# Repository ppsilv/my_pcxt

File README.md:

# my_pcxt
A try to make a pc-xt board with SRAM

## PC-XT I/O Addresses

PIC 8259
The PC/XT ISA system has one 8259 controller, and the port numbers for
configuring it are:
    Port 0x20: The master PIC's port A
    Port 0x21: The master PIC's port B

The IBM PC XT uses a single 8259 Programmable Interrupt Controller (PIC)
chip that interfaces with the system through the following I/O locations:
Ports 20h/0A0h: The command register, which is write only, and the status
register, which is read only
Ports 21h/0A1h: Corresponds to the slave PIC
8259 – The eCS Dump
The BIOS traditionally maps the 8259 PIC's eight interrupt requests (IRQs)
to interrupts 8 to 15 (0x08 to 0x0F).
The PIC manages hardware interrupt requests in an interrupt driven system
environment. When an I/O device requires service, it signals the PIC via
one of the PIC's seven interrupt request (IR) input lines. The PIC then
activates the INT line, which is connected to the CPU INTR line.

TIMER 8253
On PCs the address for timer0 (chip) is at port 40h..43h and the second
timer1 (chip) is at 50h..53h.
    Port 40h
    Port 41h
    Port 42h
    Port 43h

On x86 PCs, many video card BIOS and system BIOS will reprogram the second
counter for their own use. Reprogramming typically happens during video mode
changes, when the video BIOS may be executed, and during system management
mode and power saving state changes, when the system BIOS may be executed.
This prevents any serious alternative uses of the timer's second counter on
many x86 systems.

As stated above, Channel 0 is implemented as a counter. Typically, the
initial value of the counter is set by sending bytes to the Control, then
Data I/O Port registers (the value 36h sent to port 43h, then the low byte
to port 40h, and port 40h again for the high byte). The counter counts down
to zero, then sends a hardware interrupt (IRQ 0, INT 8) to the CPU. The
counter then resets to its initial value and begins to count down again.
The fastest possible interrupt frequency is a little over a half of a
megahertz. The slowest possible frequency, which is also the one normally
used by computers running MS-DOS or compatible operating systems, is about
18.2 Hz. Under these real mode operating systems, the BIOS accumulates the
number of INT 8 calls that it receives in real mode address 0040:006c, which
can be read by a program.

Parallel Port
    LPT1: 0x378 (or occasionally 0x3BC) (IRQ 7)
    LPT2: 0x278 (IRQ 6).

IBM defined three standard port base addresses for the parallel printer port
in the IBM PC:
Port R/W IOAddr Bits Function: Data Out W Base+0 D0-D7 8 LS TTL outputs
Status In R Base+1 S3-S7 5 LS TTL inputs
Control Out W Base+2 C0-C3 4 TTL Open Collector outputs
Common base addresses for parallel ports include:
    LPT1: 0x378 (or occasionally 0x3BC) (IRQ 7)
    LPT2: 0x278 (IRQ 6).
A parallel port is a type of interface that allows computers to connect to
various peripherals. The most common configuration for a standard parallel
port is the Centronics port, which has 25 pins.

PORTS Common I/O Port Addresses

	Port addresses are not always constant across PC, AT and PS/2
	Unless marked, port addresses are relative to PC and XT only

	000-00F  8237 DMA controller
	000 Channel 0 address register
	001 Channel 0 word count
	002 Channel 1 address register
	003 Channel 1 word count
	004 Channel 2 address register
	005 Channel 2 word count
	006 Channel 3 address register
	007 Channel 3 word count
	008 Status/command register
	009 Request register
	00A Mask register
	00B Mode register
	00C Clear MSB/LSB flip flop
	00D Master clear temp register
	00E Clear mask register
	00F Multiple mask register

	020-02F  8259A Master Programmable Interrupt Controller
	020 8259 Command port  (see 8259)
	021 8259 Interrupt mask register  (see 8259)

	040-05F  8253 or 8254 Programmable Interval Timer (PIT, see ~8253~)
	040 8253 channel 0, counter divisor
	041 8253 channel 1, RAM refresh counter
	042 8253 channel 2, Cassette and speaker functions
	043 8253 mode control  (see 8253)
	044 8254 PS/2 extended timer
	047 8254 Channel 3 control byte

	060 8255 Port A keyboard input/output buffer (output PCjr)
	061 8255 Port B output
	062 8255 Port C input
	063 8255 Command/Mode control register

//	060-06F  8042 Keyboard Controller  (AT,PS/2)
//	060 8042 Keyboard input/output buffer register
//	061 8042 system control port (for compatability with 8255)
//	064 8042 Keyboard command/status register

	070 CMOS RAM/RTC, also NMI enable/disable (AT,PS/2, see RTC)
	071 CMOS RAM data  (AT,PS/2)

	080 Manufacturer systems checkpoint port (used during POST)
	080-090  DMA Page Registers
	081 High order 4 bits of DMA channel 2 address
	082 High order 4 bits of DMA channel 3 address
	083 High order 4 bits of DMA channel 1 address

	090-097  POS/Programmable Option Select  (PS/2)
	090 Central arbitration control Port
	091 Card selection feedback
	092 System control and status register
	094 System board enable/setup register
	095 Reserved
	096 Adapter enable/setup register
	097 Reserved

	0A0 NMI Mask Register (PC,XT) (write 80h to enable NMI, 00h disable)
	0A0-0BF  Second 8259 Programmable Interrupt Controller (AT, PS/2)
	0A0 Second 8259 Command port  (see 8259)
	0A1 Second 8259 Interrupt mask register  (see 8259)

	0C0 TI SN76496 Programmable Tone/Noise Generator (PCjr)
	0C0-0DF  8237 DMA controller 2 (AT)
	0C2 DMA channel 3 selector  (see ports 6 & 82)

	0E0-0EF  Reserved

	0F0-0FF  Math coprocessor (AT, PS/2)
	0F0-0F5  PCjr Disk Controller
	0F0 Disk Controller
	0F2 Disk Controller control port
	0F4 Disk Controller status register
	0F5 Disk Controller data port

	0F8-0FF  Reserved for future microprocessor extensions

	100-10F  POS Programmable Option Select (PS/2)
	100 POS Register 0, Adapter ID byte (LSB)
	101 POS Register 1, Adapter ID byte (MSB)
	102 POS Register 2, Option select data byte 1
	    Bit 0 is card enable (CDEN)
	103 POS Register 3, Option select data byte 2
	104 POS Register 4, Option select data byte 3
	105 POS Register 5, Option select data byte 4
	    Bit 7 is (-CHCK)
	    Bit 6 is reserved
	106 POS Register 6, subaddress extension (LSB)
	107 POS Register 7, subaddress extension (MSB)

	110-1EF  System I/O channel

	170-17F  Fixed disk 1 (AT)
	170 disk 1 data
	171 disk 1 error
	172 disk 1 sector count
	173 disk 1 sector number
	174 disk 1 cylinder low
	175 disk 1 cylinder high
	176 disk 1 drive/head
	177 disk 1 status

	1F0-1FF  Fixed disk 0 (AT)
	1F0 disk 0 data
	1F1 disk 0 error
	1F2 disk 0 sector count
	1F3 disk 0 sector number
	1F4 disk 0 cylinder low
	1F5 disk 0 cylinder high
	1F6 disk 0 drive/head
	1F7 disk 0 status

	200-20F  Game Adapter (see GAME PORT or ~JOYSTICK~)

	210-217  Expansion Card Ports (XT)
	210 Write: latch expansion bus data
	    read:  verify expansion bus data
	211 Write: clear wait,test latch
	    Read:  MSB of data address
	212 Read:  LSB of data address
	213 Write: 0=enable, 1=/disable expansion unit
	214-215  Receiver Card Ports
	214 write: latch data, read: data
	215 read:  MSB of address, next read: LSB of address

	21F Reserved

	220-26F  Reserved for I/O channel

	270-27F  Third parallel port (see ~PARALLEL PORT~)
	278 data port
	279 status port
	27A control port

	280-2AF  Reserved for I/O channel

	2A2-2A3  MSM58321RS clock

	2B0-2DF  Alternate EGA, or 3270 PC video (XT, AT)

	2E0 Alternate EGA/VGA
	2E1 GPIB Adapter  (AT)

	2E2-2E3  Data acquisition adapter (AT)

	2E8-2EF  COM4 non PS/2 UART (Reserved by IBM) (see ~UART~)

	2F0-2F7  Reserved

	2F8-2FF  COM2 Second Asynchronous Adapter (see UART)
		 Primary Asynchronous Adapter for PCjr

	300-31F  Prototype Experimentation Card (except PCjr)
		 Periscope hardware debugger
	320-32F  Hard Disk Controller  (XT)
	320 Read from/Write to controller
	321 Read: Controller Status, Write: controller reset
	322 Write: generate controller select pulse
	323 Write: Pattern to DMA and interrupt mask register
	    (see ports 0F,21,C2)
	324 disk attention/status

	330-33F  Reserved for XT/370

	340-35F  Reserved for I/O channel

	360-36F  PC Network

	370-377  Floppy disk controller (except PCjr)
	372 Diskette digital output
	374 Diskette controller status
	375 Diskette controller data
	376 Diskette controller data
	377 Diskette digital input

	378-37F  Second Parallel Printer (see ~PARALLEL PORT~)
		 First Parallel Printer (see PARALLEL PORT)
	378 data port
	379 status port
	37A control port

	380-38F  Secondary Binary Synchronous Data Link Control (SDLC) adapter
	380 On board 8255 port A, internal/external sense
	381 On board 8255 port B, external modem interface
	382 On board 8255 port C, internal control and gating
	383 On board 8255 mode register
	384 On board 8253 channel square wave generator
	385 On board 8253 channel 1 inactivity time-out
	386 On board 8253 channel 2 inactivity time-out
	387 On board 8253 mode register
	388 On board 8273 read: status; Write: Command
	389 On board 8273 write: parameter; read: response
	38A On board 8273 transmit interrupt status
	38B On board 8273 receiver interrupt status
	38C On board 8273 data

	390-39F  Cluster Adapter

	3A0-3AF  Primary Binary Synchronous Data Link Control (SDLC) adapter
	3A0 On board 8255 port A, internal/external sense
	3A1 On board 8255 port B, external modem interface
	3A2 On board 8255 port C, internal control and gating
	3A3 On board 8255 mode register
	3A4 On board 8253 counter 0 unused
	3A5 On board 8253 counter 1 inactivity time-outs
	3A6 On board 8253 counter 2 inactivity time-outs
	3A7 On board 8253 mode register
	3A8 On board 8251 data
	3A9 On board 8251 command/mode/status register

	3B0-3BF Monochrome Display Adapter (write only, see ~6845~)
	3B0 port address decodes to 3B4
	3B1 port address decodes to 3B5
	3B2 port address decodes to 3B4
	3B3 port address decodes to 3B5
	3B4 6845 index register, selects which register [0-11h]
	    is to be accessed through port 3B5
	3B5 6845 data register [0-11h] selected by port 3B4,
	    registers 0C-0F may be read.  If a read occurs without
	    the adapter installed, FFh is returned.  (see 6845)
	3B6 port address decodes to 3B4
	3B7 port address decodes to 3B5
	3B8 6845 Mode control register
	3B9 reserved for color select register on color adapter
	3BA status register (read only)
	3BB reserved for light pen strobe reset

	3BC-3BF  Primary Parallel Printer Adapter (see ~PARALLEL PORT~)
	3BC parallel 1, data port
	3BD parallel 1, status port
	3BE parallel 1, control port

	3C0-3CF  EGA/VGA
	3C0 VGA attribute and sequencer register
	3C1 Other video attributes
	3C2 EGA, VGA, CGA input status 0
	3C3 Video subsystem enable
	3C4 CGA, EGA, VGA sequencer index
	3C5 CGA, EGA, VGA sequencer
	3C6 VGA video DAC PEL mask
	3C7 VGA video DAC state
	3C8 VGA video DAC PEL address
	3C9 VGA video DAC
	3CA VGA graphics 2 position
	3CC VGA graphics 1 position
	3CD VGA feature control
	3CE VGA graphics index
	3CF Other VGA graphics

	3D0-3DF Color Graphics Monitor Adapter (ports 3D0-3DB are
		write only, see 6845)
	3D0 port address decodes to 3D4
	3D1 port address decodes to 3D5
	3D2 port address decodes to 3D4
	3D3 port address decodes to 3D5
	3D4 6845 index register, selects which register [0-11h]
	    is to be accessed through port 3D5
	3D5 6845 data register [0-11h] selected by port 3D4,
	    registers 0C-0F may be read.  If a read occurs without
	    the adapter installed, FFh is returned.  (see 6845)
	3D6 port address decodes to 3D4
	3D7 port address decodes to 3D5
	3D8 6845 Mode control register (CGA, EGA, VGA, except PCjr)
	3D9 color select palette register (CGA, EGA, VGA, see 6845)
	3DA status register (read only, see 6845, PCjr VGA access)
	3DB Clear light pen latch (any write)
	3DC Preset Light pen latch
	3DF CRT/CPU page register (PCjr only)

	3E8-3EF  COM3 non PS/2 UART (Reserved by IBM) (see ~UART~)

	3F0-3F7  Floppy disk controller (except PCjr)
	3F0 Diskette controller status A
	3F1 Diskette controller status B
	3F2 controller control port
	3F4 controller status register
	3F5 data register (write 1-9 byte command, see INT 13)
	3F6 Diskette controller data
	3F7 Diskette digital input

	3F8-3FF  COM1 Primary Asynchronous Adapter  (see ~UART~)

	3220-3227  PS/2 COM3 (see UART)
	3228-322F  PS/2 COM4 (see UART)
	4220-4227  PS/2 COM5 (see UART)
	4228-422F  PS/2 COM6 (see UART)
	5220-5227  PS/2 COM7 (see UART)
	5228-522F  PS/2 COM8 (see UART)

	- many cards designed for the ISA BUS only uses the lower 10 bits
	  of the port address but some ISA adapters use addresses beyond
	  3FF.  Any address that matches in the lower 10 bits will decode
	  to the same card.   It is up to the adapters to resolve or ignore
	  the high bits of the port addresses.   An example would be the
	  Cluster adapter that has a port address of 390h.  The second
	  cluster adapter has a port address of 790h which resolves to
	  the same port address with the cards determining which one
	  actually gets the data.

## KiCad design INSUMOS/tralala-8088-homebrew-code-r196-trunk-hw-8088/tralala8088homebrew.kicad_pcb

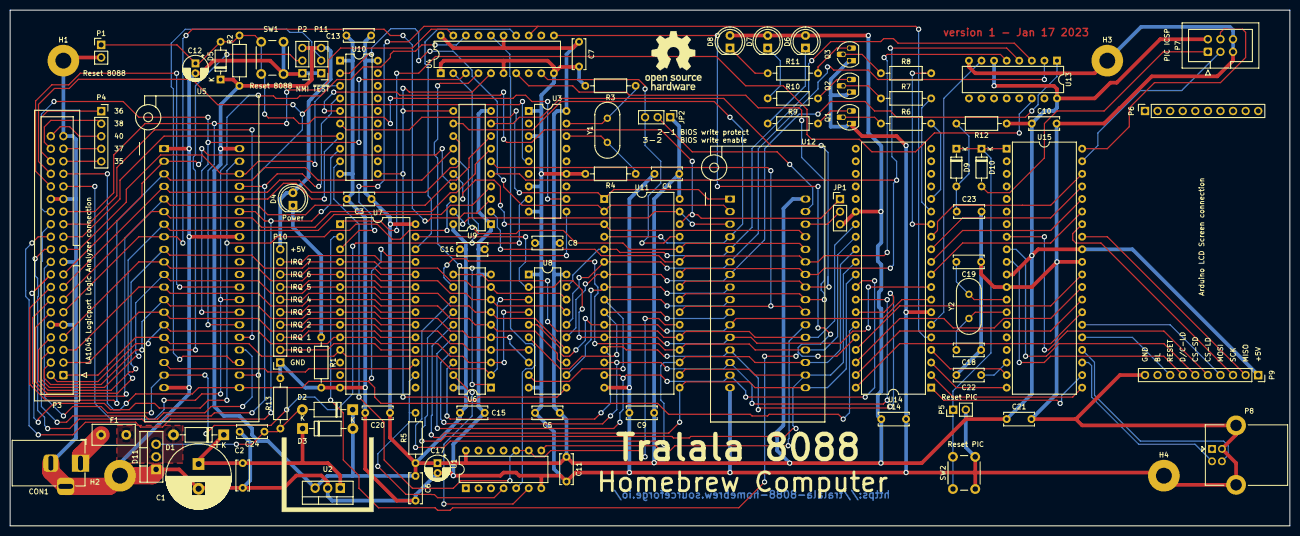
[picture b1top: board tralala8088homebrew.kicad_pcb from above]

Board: 2 copper layers, 258.4 x 104.1 mm, 89 parts (0 on the bottom side), 139 nets.

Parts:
C1: 1000 uF; CP_Radial_D13.0mm_P5.00mm
C2: 330nF; C_Disc_D6.0mm_W2.5mm_P5.00mm
C3, C4, C5, C6, C7, C8, C9, C10, C11, C13, C14, C15, C16, C20, C21, C23, C24: 100nF; C_Disc_D6.0mm_W2.5mm_P5.00mm
C12: 4.7uF; CP_Radial_D5.0mm_P2.00mm
C17: 100uF; CP_Radial_D5.0mm_P2.00mm
C18, C19: 22pF; C_Disc_D6.0mm_W2.5mm_P5.00mm
C22: 220nF; C_Disc_D6.0mm_W2.5mm_P5.00mm
CON1: BARREL_JACK; BarrelJack_Horizontal
D1: 1N4002; D_DO-41_SOD81_P10.16mm_Horizontal
D2: 5.6 V; D_DO-41_SOD81_P10.16mm_Horizontal
D3: D; D_DO-41_SOD81_P10.16mm_Horizontal
D4: Power; LED_D5.0mm
D5, D9, D10: 1N4148; D_DO-35_SOD27_P7.62mm_Horizontal
D6: LED_RED; LED_D5.0mm
D7: LED_YELLOW; LED_D5.0mm
D8: LED_GREEN; LED_D5.0mm
D11: BT151-500RT.127; TO-220-3_Vertical
F1: 30R160U; Fuse_Littelfuse_395Series
H1, H2, H3, H4: MountingHole_Pad; MountingHole_3.2mm_M3_Pad
JP1: ROM type sel; PinHeader_1x03_P2.54mm_Vertical
JP2: Flash Write Protect; PinHeader_1x03_P2.54mm_Vertical
P1, P5: Conn_01x02_Male; PinHeader_1x02_P2.54mm_Vertical
P2: NMI; PinHeader_1x03_P2.54mm_Vertical
P3: LA1034 Logicport Connection; IDC-Header_2x20_P2.54mm_Vertical
P4: Conn_01x05_Female; PinSocket_1x05_P2.54mm_Vertical
P6, P9: CONN_01X10; PinSocket_1x10_P2.54mm_Vertical
P7: PIC ISP; IDC-Header_2x03_P2.54mm_Vertical
P8: USB_B; USB_B_Lumberg_2411_02_Horizontal
P10: Conn_01x10; PinSocket_1x10_P2.54mm_Vertical
P11: ~{TEST}; PinHeader_1x03_P2.54mm_Vertical
Q1, Q2, Q3: 2N3904; TO-92_HandSolder
R1: 270; R_Axial_DIN0207_L6.3mm_D2.5mm_P10.16mm_Horizontal
R2, R6, R7, R8: 10K; R_Axial_DIN0207_L6.3mm_D2.5mm_P10.16mm_Horizontal
R3, R4: 510; R_Axial_DIN0207_L6.3mm_D2.5mm_P10.16mm_Horizontal
R5: 4.7K; R_Axial_DIN0207_L6.3mm_D2.5mm_P10.16mm_Horizontal
R9, R10, R11: 100; R_Axial_DIN0207_L6.3mm_D2.5mm_P10.16mm_Horizontal
R12: 47K; R_Axial_DIN0207_L6.3mm_D2.5mm_P10.16mm_Horizontal
R13: 1k; R_Axial_DIN0207_L6.3mm_D2.5mm_P10.16mm_Horizontal
SW1: RESET_8088; SW_PUSH_6mm_H5mm
SW2: RESET_PIC; SW_PUSH_6mm_H5mm
U1: 74HCT00; DIP-14_W7.62mm
U2: 7805; TO-220-3_Vertical
U3: 8284; DIP-18_W7.62mm
U4: 8288; DIP-20_W7.62mm
U5: 8088; DIP_Socket-40_W11.9_W12.7_W15.24_W17.78_W18.5_3M_240-1280-0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
U6: 74HCT245; DIP-20_W7.62mm
U7: 8259A; DIP-28_W15.24mm
U8, U9, U10: 74HCT373; DIP-20_W7.62mm
U11: AS6C4008; DIP-32_W15.24mm
U12: SST39SF040; DIP_Socket-32_W11.9_W12.7_W15.24_W17.78_W18.5_3M_232-1285-0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
U13: 74HCT138; DIP-16_W7.62mm
U14: 82C55A; DIP-40_W15.24mm
U15: PIC18(L)F4550-I/P or PIC18(L)F4553-I/P; DIP-40_W15.24mm
Y1: 6-30 MHz; Crystal_HC49-U_Vertical
Y2: 20.000 MHz; Crystal_HC49-U_Vertical

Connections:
+5V: C3.1, C4.1, C5.1, C6.1, C7.1, C8.1, C9.1, C10.1, C11.1, C13.1, C14.1, C15.1, C16.1, C17.1, C20.1, C21.1, D2.1 (K), D3.2 (A), D4.2 (A), D5.1 (K), D6.2 (A), D7.2 (A), D8.2 (A), JP1.3 (B), JP2.1 (A), P2.3, P7.2, P9.1, P10.10, P11.3, R2.1, R5.1, R12.1, U1.14 (VCC), U2.3 (OUT), U3.18 (VCC), U4.15 (CEN), U4.20 (VCC), U5.40 (VCC), U6.20 (VCC), U7.28 (VCC), U8.20 (VCC), U9.20 (VCC), U10.20 (VCC), U11.32 (VCC), U12.32 (VCC), U13.6 (E3), U13.16 (VCC), U14.26 (VCC), U15.11 (VDD), U15.32 (VDD)
/8088 System/8255_CS: U13.7 (O7), U14.6 (~CS)
/8088 System/8259A_CS: U7.1 (~CS), U13.14 (O1)
/8088 System/8259A_SP_EN: R5.2, U1.4, U7.16 (~SP/~EN)
/8088 System/A8: P3.11, U5.8 (A8), U9.3 (D0)
/8088 System/A9: P3.12, U5.7 (A9), U9.4 (D1)
/8088 System/A10: P3.13, U5.6 (A10), U9.7 (D2)
/8088 System/A11: P3.14, U5.5 (A11), U9.8 (D3)
/8088 System/A12: P3.15, U5.4 (A12), U9.13 (D4)
/8088 System/A13: P3.16, U5.3 (A13), U9.14 (D5)
/8088 System/A14: P3.17, U5.2 (A14), U9.17 (D6)
/8088 System/A15: P3.18, U5.39 (A15), U9.18 (D7)
/8088 System/A16_S3: P3.21, U5.38 (A16/S3), U10.3 (D0)
/8088 System/A17_S4: P3.22, U5.37 (A17/S4), U10.4 (D1)
/8088 System/A18_S5: P3.23, U5.36 (A18/S5), U10.7 (D2)
/8088 System/A19_S6: P3.24, U5.35 (A19/S6), U10.8 (D3)
/8088 System/AD0: P3.1, U5.16 (AD0), U6.2 (A0), U7.11 (D0), U8.3 (D0)
/8088 System/AD1: P3.2, U5.15 (AD1), U6.3 (A1), U7.10 (D1), U8.4 (D1)
/8088 System/AD2: P3.3, U5.14 (AD2), U6.4 (A2), U7.9 (D2), U8.7 (D2)
/8088 System/AD3: P3.4, U5.13 (AD3), U6.5 (A3), U7.8 (D3), U8.8 (D3)
/8088 System/AD4: P3.5, U5.12 (AD4), U6.6 (A4), U7.7 (D4), U8.13 (D4)
/8088 System/AD5: P3.6, U5.11 (AD5), U6.7 (A5), U7.6 (D5), U8.14 (D5)
/8088 System/AD6: P3.7, U5.10 (AD6), U6.8 (A6), U7.5 (D6), U8.17 (D6)
/8088 System/AD7: P3.8, U5.9 (AD7), U6.9 (A7), U7.4 (D7), U8.18 (D7)
/8088 System/ALE: U4.5 (ALE), U8.11 (LE), U9.11 (LE), U10.11 (LE)
/8088 System/BUF_A0: U7.27 (A0), U8.2 (O0), U11.12 (A0), U12.12 (A0), U14.9 (A0)
/8088 System/BUF_A1: U8.5 (O1), U11.11 (A1), U12.11 (A1), U14.8 (A1)
/8088 System/BUF_A2: U8.6 (O2), U11.10 (A2), U12.10 (A2)
/8088 System/BUF_A3: U8.9 (O3), U11.9 (A3), U12.9 (A3)
/8088 System/BUF_A4: U8.12 (O4), U11.8 (A4), U12.8 (A4)
/8088 System/BUF_A5: U8.15 (O5), U11.7 (A5), U12.7 (A5), U13.1 (A0)
/8088 System/BUF_A6: U8.16 (O6), U11.6 (A6), U12.6 (A6), U13.2 (A1)
/8088 System/BUF_A7: U8.19 (O7), U11.5 (A7), U12.5 (A7), U13.3 (A2)
/8088 System/BUF_A8: U9.2 (O0), U11.27 (A8), U12.27 (A8), U13.5 (E2)
/8088 System/BUF_A9: U9.5 (O1), U11.26 (A9), U12.26 (A9), U13.4 (E1)
/8088 System/BUF_A10: U9.6 (O2), U11.23 (A10), U12.23 (A10)
/8088 System/BUF_A11: U9.9 (O3), U11.25 (A11), U12.25 (A11)
/8088 System/BUF_A12: U9.12 (O4), U11.4 (A12), U12.4 (A12)
/8088 System/BUF_A13: U9.15 (O5), U11.28 (A13), U12.28 (A13)
/8088 System/BUF_A14: U9.16 (O6), U11.3 (A14), U12.29 (A14)
/8088 System/BUF_A15: U9.19 (O7), U11.31 (A15), U12.3 (A15)
/8088 System/BUF_A16: U10.2 (O0), U11.2 (A16), U12.2 (A16)
/8088 System/BUF_A17: JP1.1 (A), U10.5 (O1), U11.30 (A17)
/8088 System/BUF_A18: U10.6 (O2), U11.1 (A18), U12.1 (A18)
/8088 System/BUF_A19: U1.9, U1.10, U10.9 (O3), U11.22 (CE#)
/8088 System/BUF_D0: U6.18 (B0), U11.13 (DQ0), U12.13 (D0), U14.34 (D0)
/8088 System/BUF_D1: U6.17 (B1), U11.14 (DQ1), U12.14 (D1), U14.33 (D1)
/8088 System/BUF_D2: U6.16 (B2), U11.15 (DQ2), U12.15 (D2), U14.32 (D2)
/8088 System/BUF_D3: U6.15 (B3), U11.17 (DQ3), U12.17 (D3), U14.31 (D3)
/8088 System/BUF_D4: U6.14 (B4), U11.18 (DQ4), U12.18 (D4), U14.30 (D4)
/8088 System/BUF_D5: U6.13 (B5), U11.19 (DQ5), U12.19 (D5), U14.29 (D5)
/8088 System/BUF_D6: U6.12 (B6), U11.20 (DQ6), U12.20 (D6), U14.28 (D6)
/8088 System/BUF_D7: U6.11 (B7), U11.21 (DQ7), U12.21 (D7), U14.27 (D7)
/8088 System/CLK: P3.20, U3.8 (CLK), U4.2 (CLK), U5.19 (CLK)
/8088 System/DEN: U1.5, U4.16 (DEN)
/8088 System/DTR: U4.4 (DT/~R), U6.1 (A->B)
/8088 System/ICH_ACK: U14.11 (PC6), U15.36 (RB3/AN9/CCP2/VPO)
/8088 System/ICH_D0: U14.4 (PA0), U15.19 (SPP0/RD0)
/8088 System/ICH_D1: U14.3 (PA1), U15.20 (SPP1/RD1)
/8088 System/ICH_D2: U14.2 (PA2), U15.21 (SPP2/RD2)
/8088 System/ICH_D3: U14.1 (PA3), U15.22 (SPP3/RD3)
/8088 System/ICH_D4: U14.40 (PA4), U15.27 (SPP4/RD4)
/8088 System/ICH_D5: U14.39 (PA5), U15.28 (P1B/SPP5/RD5)
/8088 System/ICH_D6: U14.38 (PA6), U15.29 (P1C/SPP6/RD6)
/8088 System/ICH_D7: U14.37 (PA7), U15.30 (P1D/SPP7/RD7)
/8088 System/ICH_IBF: U14.12 (PC5), U15.37 (RB4/AN11/KBI0/CSSPP)
/8088 System/ICH_OBF: U14.10 (PC7), U15.35 (RB2/AN8/INT2/VMO)
/8088 System/ICH_STB: U14.13 (PC4), U15.38 (RB5/KBI1/PGM)
/8088 System/INTA: U4.14 (~INTA), U7.26 (~INTA)
/8088 System/INTR: U5.18 (INTR), U7.17 (INT)
/8088 System/IORC: U4.13 (~IORC), U7.3 (~RD), U14.5 (~RD)
/8088 System/IOWC: U4.11 (~IOWC), U7.2 (~WR), U14.36 (~WR)
/8088 System/IRQ0: P10.2, U7.18 (IR0)
/8088 System/IRQ1: P10.3, U7.19 (IR1)
/8088 System/IRQ2: P10.4, U7.20 (IR2)
/8088 System/IRQ3: P10.5, U7.21 (IR3)
/8088 System/IRQ4: P10.6, U7.22 (IR4)
/8088 System/IRQ5: P10.7, U7.23 (IR5)
/8088 System/IRQ6: P10.8, U7.24 (IR6)
/8088 System/IRQ7: P10.9, U7.25 (IR7)
/8088 System/LED_GREEN: R8.2, U14.14 (PC0)
/8088 System/LED_RED: R6.2, U14.16 (PC2)
/8088 System/LED_YELLOW: R7.2, U14.15 (PC1)
/8088 System/LOCK: P3.32, U5.29 (~LOCK)
/8088 System/MRDC: U4.7 (~MRDC), U11.24 (OE#), U12.24 (OE)
/8088 System/MWTC: JP2.3 (B), U4.9 (~MWTC), U11.29 (WE#)
/8088 System/QS0: P3.25, U5.25 (QS0)
/8088 System/QS1: P3.26, U5.24 (QS1)
/8088 System/READY: P3.34, U3.5 (READY), U5.22 (READY)
/8088 System/RESET: P3.33, U3.10 (RESET), U5.21 (RESET), U14.35 (RESET)
/8088 System/S0: P3.27, U4.19 (~S0), U5.26 (~S0)
/8088 System/S1: P3.28, U4.3 (~S1), U5.27 (~S1)
/8088 System/S2: P3.31, U4.18 (~S2), U5.28 (~S2)
/PIC and IO/PIC_PGC: P7.3, U15.39 (RB6/KBI2/PGC)
/PIC and IO/PIC_PGD: P7.4, U15.40 (RB7/KBI3/PGD)
/PIC and IO/PIC_VPP: D10.2 (A), P7.1
/PIC and IO/TFT_D_C: P9.7, U15.10 (OESPP/AN7/RE2)
/PIC and IO/TFT_LCD_CS: P9.5, U15.8 (CK1SPP/AN5/RE0)
/PIC and IO/TFT_MISO: P9.2, U15.33 (RB0/AN12/INT0/FLT0/SDI/SDA)
/PIC and IO/TFT_MOSI: P9.4, U15.26 (SDO/RX/DT/RC7)
/PIC and IO/TFT_Reset: P9.8, U15.25 (TX/CK/RC6)
/PIC and IO/TFT_SCK: P9.3, U15.34 (RB1/AN10/INT1/SCK/SCL)
/PIC and IO/TFT_SD_CS: P9.6, U15.9 (CK2SPP/AN6/RE1)
/Power and Clock/Vin_fused: D1.2 (A), D11.2 (A), F1.2
GND: C1.2, C2.2, C3.2, C4.2, C5.2, C6.2, C7.2, C8.2, C9.2, C10.2, C11.2, C12.2, C13.2, C14.2, C15.2, C16.2, C17.2, C18.1, C19.1, C20.2, C21.2, C22.2, C23.2, C24.2, CON1.2, CON1.3, D11.1 (K), H1.1, H2.1, H3.1, H4.1, P1.2, P2.1, P3.9, P3.10, P3.19, P3.29, P3.30, P3.39, P5.2, P7.5, P7.6, P8.4 (GND), P8.5 (Shield), P9.10, P10.1, P11.1, Q1.1 (E), Q2.1 (E), Q3.1 (E), R1.2, R3.2, R4.2, R13.2, SW1.1, SW2.2, U1.7 (GND), U2.2 (GND), U3.1 (CSYNC), U3.3 (~AEN1), U3.7 (~AEN2), U3.9 (GND), U3.13 (F/~C), U4.1 (IOB), U4.6 (~AEN), U4.10 (GND), U5.1 (GND), U5.20 (GND), U5.33 (MN/~MX), U6.10 (GND), U7.14 (GND), U8.1 (OE), U8.10 (GND), U9.1 (OE), U9.10 (GND), U10.1 (OE), U10.10 (GND), U11.16 (VSS), U12.16 (GND), U13.8 (GND), U14.7 (GND), U15.12 (VSS), U15.31 (VSS)
unnamed: C1.1, C2.1, D1.1 (K), D3.1 (K), U2.1 (IN)
unnamed: C12.1, D5.2 (A), P1.1, R2.2, SW1.2, U3.11 (~RES)
unnamed: C18.2, U15.14 (RA6/OSC2/CLKO), Y2.1
unnamed: C19.2, U15.13 (OSC1/CLKI), Y2.2
unnamed: C22.1, U15.18 (VUSB)
unnamed: C23.1, D9.2 (A), R12.2
unnamed: C24.1, D2.2 (A), D11.3 (G), R13.1
unnamed: CON1.1, F1.1
unnamed: D4.1 (K), R1.1
unnamed: D6.1 (K), R9.1
unnamed: D7.1 (K), R10.1
unnamed: D8.1 (K), R11.1
unnamed: D9.1 (K), D10.1 (K), P5.1, SW2.1, U15.1 (Vpp/~MCLR/RE3)
unnamed: JP1.2 (C), U12.30 (A17)
unnamed: JP2.2 (C), U12.31 (PGM)
unnamed: P2.2, U5.17 (NMI)
unnamed: P3.35, P4.5
unnamed: P3.36, P4.1
unnamed: P3.37, P4.4
unnamed: P3.38, P4.2
unnamed: P3.40, P4.3
unnamed: P8.2 (D-), U15.23 (VM/D-/RC4)
unnamed: P8.3 (D+), U15.24 (VP/D+/RC5)
unnamed: P11.2, U5.23 (~TEST)
unnamed: Q1.2 (B), R6.1
unnamed: Q1.3 (C), R9.2
unnamed: Q2.2 (B), R7.1
unnamed: Q2.3 (C), R10.2
unnamed: Q3.2 (B), R8.1
unnamed: Q3.3 (C), R11.2
unnamed: R3.1, U3.17 (X1), Y1.2
unnamed: R4.1, U3.16 (X2), Y1.1
unnamed: U1.6, U6.19 (CE)
unnamed: U1.8, U12.22 (CE)

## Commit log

2024-11-21 Schematics and gal firmaware finished
2024-11-22 Functional Test
2024-11-22 Teste de existenciad e memoria
2024-11-22 Teste com a RS232
2024-11-22 updating schematics
2024-11-23 Updating after cpu config finished
2024-11-24 Versao estavel de testes
2024-11-24 Inicio da bios apos testes
2024-11-24 Rename test.asm to mybios.asm
2024-11-24 Updating...
2024-11-27 Implemented 8259 e 8253
2024-11-29 Updating schematic
2024-11-30 Updating code...
2024-12-01 Updating implemented cin cout
2024-12-02 Implemented edit memory
2024-12-03 Implemented and tested fillmemory
2024-12-08 Implemented ch376s
2025-04-02 Added IBM 5150 manual

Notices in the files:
INSUMOS/tralala-8088-homebrew-code-r196-trunk-hw-8088/tralala8088homebrew.kicad_pcb:
Copyright (C) 2016, 2017, 2022, 2023 Nikolay Nikolov
http://creativecommons.org/licenses/by-sa/3.0/ or send a letter to Creative Commons,
This work is licensed under the Creative Commons Attribution-ShareAlike 3.0 Unported
